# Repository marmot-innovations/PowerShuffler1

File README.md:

# PowerShuffler1
Summary: PowerShuffler1 is a HV isolated DC-DC charger PCBA for balancing weak cells within a large battery stack of Li-Ion cells.

Theory of operation: In a battery stack with 99 lithium-ion cells in series, there might be 1 or 2 weak cells that limit the usability of the entire battery pack. Let's assume the 99 li-ion cells are arranged in groups of 9 and there are certain groups that contain cells which are stronger than others. PowerShuffler1 is a PCBA that will piggy-back on top of the existing BMS that comes with the battery pack and draw power from the stronger group in order to charge up the 1 weak cell wherever it sits in the series of 99 cells. PowerShuffler1 has built-in intelligence not to over-discharge the stronger group by measuring the voltage of the 1 weak cell as it rises, and compares it to 1/9th of the stronger group's total voltage as it falls to within a certain threshold. Pre-programmed hysteresis prevents excessive start-stop charging as the cells are put through normal usage during the time when the existing BMS kicks in. Although intrusive, PowerShuffler1 is meant to be a diagnostics tool to verify and characterize weak cells within a battery stack on top of a pre-existing BMS. It does not replace the need for servicing the battery pack or using a better BMS down the road. PowerShuffler1 has no wired or wireless communication, which is not accessible anyway if piggy-backed within a battery pack enclosure.

Included in this project are:
1. Firmware for master MCU
2. Firmware for client MCU
3. PCB design for PCBA

Read the individual README for further details. Pictures will be added later to provide instructions for programming and installation, as well as board modifications where needed. Test data will be provided eventually.

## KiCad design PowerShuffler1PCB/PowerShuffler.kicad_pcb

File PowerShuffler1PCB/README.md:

## PowerShuffler 1.0 PCB design schematic, layout, Gerbers, and BOM  
KiCAD 5.0.0 for PCB design  
Microsoft Excel web for BOM  
No 3D model  
No XY pick and place Centroid  
No ODB++  
No footprint library  
No schematic library

Design bugs and comments:  
1. S2 pins 3 and 4 are swapped. Use wire wrap to un-swap them.
2. F2 will drop about 0.1V under full 500mA load when charging. No way to measure OCV in this version. Manually take measurements and compensate by adjusting master MCU.
3. R12 cannot be switched off to stop charging. Everytime the client MCU is turned on to take a measurement it will move energy.
4. To program master MCU, remove R6 and C7 first, then replace them once programming is completed. These components will put too much load on ISP TPI programmer.
5. To program client MCU, remove C24 and (optionally) R22 first, then replace them once completed. These components will put too much load on ISP TPI programmer.
6. J2 and J4 do not need soldered headers for programming. Just shove a 5-pin 0.1" straight strip header into it to establish electrical contact. Look up "sneaky footprints PCB" on the web.
7. Mounting holes are for 4-40 screws and stand-offs.
8. Peak 75% efficiency during max charge rate as measured.
9. Less than 0.5mA current draw from input when idle, not charging.

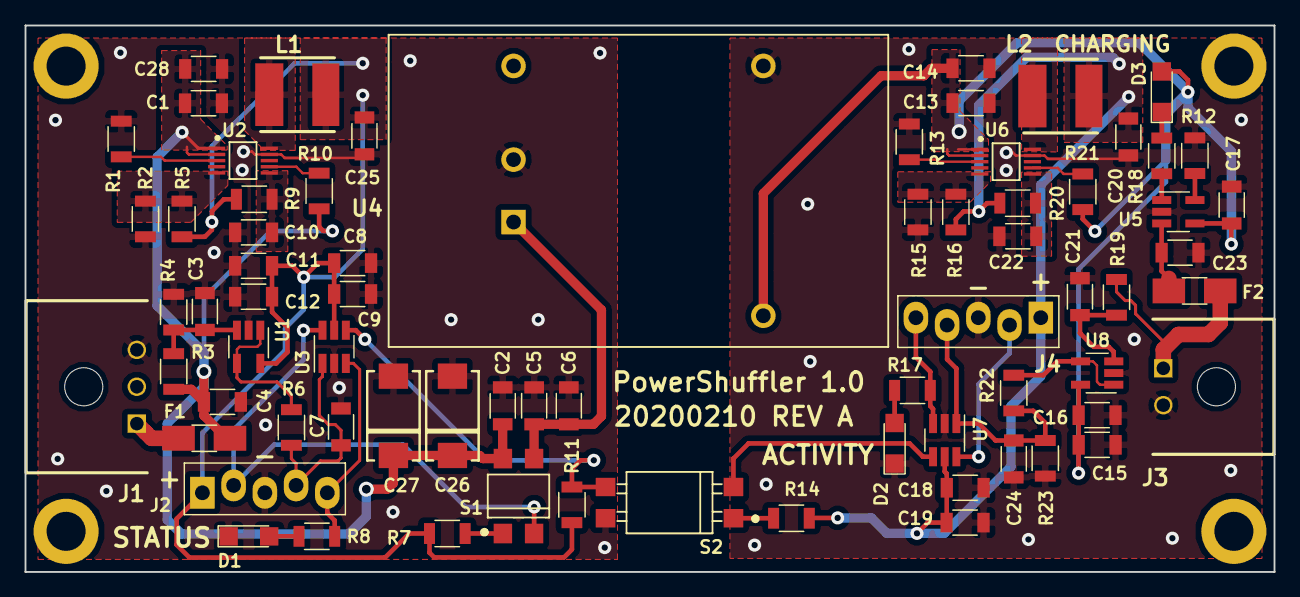
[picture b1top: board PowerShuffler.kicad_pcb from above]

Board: 4 copper layers, 101.6 x 44.5 mm, 76 parts (0 on the bottom side), 39 nets.

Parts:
C1, C3, C5, C7, C8, C11, C13, C15, C18, C21, C24: 1u; C_1206
C2, C6, C9, C12, C14, C16, C19, C28: 0.1u; C_1206
C4, C20, C25: 10u; C_1206
C10, C22: 0.22u; C_1206
C17, C23: 4.7u; C_1206
C26, C27: 15u; 2917
D1, D2, D3: LED; LED_1206
F1, F2: Fuse; Fuse_SMD1206_HandSoldering
J1: Conn_01x03; Molex_Microfit3_Header_3pin_Angled_43650
J2, J4: Conn_01x05; Staggered_ICSP_5x2.54mm_Straight
J3: Conn_01x02; Molex_Microfit3_Header_2pin_Angled_43650
L1, L2: 680u; SMD_Inductor_Shielded_6x6mm
MNT1, MNT2, MNT3, MNT4: MountingHole; 3mm_hole
R1, R10, R13, R21: 191k; R_1206
R2, R15: 49.9k; R_1206
R3: 150k; R_1206
R4, R22: 18.7k; R_1206
R5, R16: 158k; R_1206
R6, R7, R8, R14, R17, R19: 390; R_1206
R9, R20: 22.1; R_1206
R11, R12: 2k; R_1206
R18: 470; R_1206
R23: 56.2k; R_1206
S1: SSR4; SMD4_SSR_CPC1002N
S2: OPTOSOLO; SMD4_TL241AF-SSR_0.1_12x5mm
U1, U8: MCP6401; SOT-23-5_HandSoldering
U2, U6: SWITCHDCDCLOPOW; 10-μMAX_3x3mm
U3, U7: ATTINY; SOT-23-6_Handsoldering
U4: ISOLATEDDCDC; NSD05-S_6-DIP_1x1.6inch
U5: MCP73831; SOT-23-5_HandSoldering

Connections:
+3.3VA: C18.1, C19.1, C20.1, J4.1, L2.2, R14.1, R16.1, R20.1, U7.5
+3V3: C8.1, C9.1, C11.1, C12.1, C25.1, J2.1, L1.2, R5.1, R7.2, R9.1, R11.1, U1.5, U3.5
+5VA: C13.1, C14.1, C15.1, C16.1, C17.1, D3.2, R21.2, U4.3, U5.4, U6.1, U6.2, U8.5
+36V: C1.1, C2.1, C4.1, C26.1, C27.1, C28.1, F1.1, R3.1, R10.2, S1.4, U2.1, U2.2
/36VSWITCH: C5.1, C6.1, S1.3, U4.1
/PB0_1: C7.1, J2.4, R6.1, U3.1
/PB0_2: C24.1, J4.4, R22.2, R23.1, U7.1
/PB1_1: J2.5, R8.1, U3.3
/PB1_2: J4.5, R17.1, U7.3
/PB2_1: R11.2, S2.3, U3.4
/PB2_2: S2.2, U7.4
/PB3_1: J2.2, S1.2, U3.6
/PB3_2: J4.2, U7.6
/VBATT: F2.1, J3.1, R19.2
/VBATTFUSE: C23.1, F2.2, U5.3
/VSUBSHEET: C3.1, R3.2, R4.1, U1.3
GND: C1.2, C2.2, C3.2, C4.2, C5.2, C6.2, C7.2, C8.2, C9.2, C10.2, C11.2, C12.2, C25.2, C26.2, C27.2, C28.2, D1.1, J1.3, J2.3, R1.2, R2.1, R4.2, S2.4, U1.2, U2.9, U3.2, U4.2
GNDA: C13.2, C14.2, C15.2, C16.2, C17.2, C18.2, C19.2, C20.2, C21.2, C22.2, C23.2, C24.2, D2.1, J3.2, J4.3, R12.1, R13.2, R15.1, R23.2, U4.4, U5.2, U6.9, U7.2, U8.2
unnamed: C10.1, R9.2, U2.6
unnamed: C21.1, R19.1, U8.3
unnamed: C22.1, R20.2, U6.6
unnamed: D1.2, R8.2
unnamed: D2.2, R17.2
unnamed: D3.1, R18.2
unnamed: F1.2, J1.1
unnamed: L1.1, U2.10
unnamed: L2.1, U6.10
unnamed: R1.1, U2.3
unnamed: R2.2, R5.2, U2.5
unnamed: R6.2, U1.1, U1.4
unnamed: R7.1, S1.1
unnamed: R10.1, U2.7
unnamed: R12.2, U5.5
unnamed: R13.1, U6.3
unnamed: R14.2, S2.1
unnamed: R15.2, R16.2, U6.5
unnamed: R18.1, U5.1
unnamed: R21.1, U6.7
unnamed: R22.1, U8.1, U8.4

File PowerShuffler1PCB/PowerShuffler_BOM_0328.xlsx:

ref | QTY | value5 | footprint | Manuf P/N | Digikey P/N | description
U2, U6 | 2 | SWITCHDCDCLOPOW | BMB:10-μMAX_3x3mm | MAX17550AUB+ | MAX17550AUB+-ND | IC REG BUCK ADJ 25MA 10UMAX
C26, C27 | 2 | 15u | BMB:2917 | TR3E156M050C0300‎ | 718-1785-1-ND‎ | CAP TANT 15UF 20% 50V 2917
J3 | 1 | Conn_01x02 | BMB:Molex_Microfit3_Header_2pin_Angled_43650 | 0436500200‎ | WM1860-ND | CONN HEADER R/A 2POS 3MM
J1 | 1 | Conn_01x03 | BMB:Molex_Microfit3_Header_3pin_Angled_43650 | 0436500301‎ | ‎WM1866-ND‎ | CONN HEADER R/A 3POS 3MM
U4 | 1 | ISOLATEDDCDC | BMB:NSD05-S_6-DIP_1x1.6inch | NSD05-48S5‎ | 1866-3621-ND‎ | DC DC CONVERTER 5V 5W isolated
L1, L2 | 2 | 680u | BMB:SMD_Inductor_Shielded_6x6mm | VLS6045EX-681M | ‎445-180928-1-ND | FIX IND 680UH 320MA 2.95OHM SMD
S1 | 1 | SSR4 | BMB:SMD4_SSR_CPC1002N | CPC1002NTR‎ | CLA230CT-ND | SSR RELAY SPST-NO 700MA 0-60V
S2 | 1 | OPTOSOLO | BMB:SMD4_TL241AF-SSR_0.1_12x5mm | ‎LTV-816S | ‎160-1361-5-ND | OPTOISOLATR 5KV TRANSISTOR 4-SMD
J2 | 1 | Conn_01x05 | BMB:Staggered_ICSP_5x2.54mm_Straight |  |  | DO NOT POPULATE
J4 | 1 | Conn_01x05 | BMB:Staggered_ICSP_5x2.54mm_Straight |  |  | DO NOT POPULATE
C12, C14, C16, C19, C2, C28, C6, C9 | 8 | 0.1u | Capacitors_SMD:C_1206 | CL31B104KCFNNNE‎ | 1276-1151-1-ND | CAP CER 0.1UF 100V X7R 1206
C10, C22 | 2 | 0.22u | Capacitors_SMD:C_1206 | CL31B224KBFNNNE‎ | 1276-1106-1-ND
C20, C25, C4 | 3 | 10u | Capacitors_SMD:C_1206 | CL31B106KBHNNNE‎ | 1276-6767-1-ND | CAP CER 10UF 50V X7R 1206
C1, C11, C13, C15, C18, C21, C24, C3, C5, C7, C8 | 11 | 1u | Capacitors_SMD:C_1206 | CL31B105KBHNNNE‎ | ‎1276-1068-1-ND‎ | CAP CER 1UF 50V X7R 1206
C17, C23 | 2 | 4.7u | Capacitors_SMD:C_1206 | CL31B475KAHNNWE‎ | ‎1276-3178-1-ND
F1 | 1 | Fuse | Fuse_Holders_and_Fuses:Fuse_SMD1206_HandSoldering | C1F 3 | 507-1883-1-ND | FUSE 3.0A 125VAC FAST 1206
F2 | 1 | Fuse | Fuse_Holders_and_Fuses:Fuse_SMD1206_HandSoldering | C1F 1.5 | 507-1880-1-ND | FUSE 1.5A 125VAC FAST 1206
D1 | 1 | LED | LEDs:LED_1206 | 150120GS75000‎ | ‎732-4990-1-ND‎ | LED GREEN CLEAR 1206 SMD
D2, D3 | 2 | LED | LEDs:LED_1206 | 150120RS75000‎ | ‎732-4991-1-ND | LED RED CLEAR 1206 SMD
R20, R9 | 2 | 22.1 | Resistors_SMD:R_1206 | RMCF1206FT22R1‎ | ‎RMCF1206FT22R1CT-ND‎
R14, R17, R19, R6, R7, R8 | 6 | 390 | Resistors_SMD:R_1206 | RMCF1206JT390R‎ | ‎RMCF1206JT390RCT-ND‎
R18 | 1 | 470 | Resistors_SMD:R_1206 | RMCF1206JT470R‎ | ‎RMCF1206JT470RCT-ND‎
R3 | 1 | 210k | Resistors_SMD:R_1206 | ERA-8AEB2103V | P210KBCCT-ND | RES SMD 210K OHM 0.1% 1/4W 1206
R16, R5 | 2 | 158k | Resistors_SMD:R_1206 | RMCF1206FT158K‎ | ‎RMCF1206FT158KCT-ND‎ | RES 158K OHM 1% 1/4W 1206
R22 | 1 | 18.7k | Resistors_SMD:R_1206 | ‎ERA-8AEB1872V‎ | ‎P18.7KBCCT-ND‎ | RES SMD 18.7K OHM 0.1% 1/4W 1206
R4 | 1 | 19.1k | Resistors_SMD:R_1206 | ‎RT1206BRD0719K1L | YAG2018CT-ND‎ | RES SMD 19.1K OHM 0.1% 1/4W 1206
R1, R10, R13, R21 | 4 | 191k | Resistors_SMD:R_1206 | MCR18ERTF1913‎ | ‎RHM191KCJCT-ND‎ | RES SMD 191K OHM 1% 1/4W 1206
R11, R12, R18 | 3 | 2k | Resistors_SMD:R_1206 | RMCF1206FG2K00‎ | ‎RMCF1206FG2K00CT-ND‎ | RES 2K OHM 1% 1/4W 1206
R15, R2 | 2 | 49.9k | Resistors_SMD:R_1206 | RMCF1206FT49K9‎ | ‎RMCF1206FT49K9CT-ND‎ | RES 49.9K OHM 1% 1/4W 1206
R23 | 1 | 56.2k | Resistors_SMD:R_1206 | RT1206BRD0756K2L‎ | YAG2060CT-ND | RES SMD 56.2K OHM 0.1% 1/4W 1206
U1, U8 | 2 | MCP6401 | TO_SOT_Packages_SMD:SOT-23-5_HandSoldering | ‎MCP6401T-H/OT‎ | MCP6401T-H/OTCT-ND‎ | IC OPAMP GP 1 CIRCUIT SOT23-5 hi temp
U5 | 1 | MCP73831 | TO_SOT_Packages_SMD:SOT-23-5_HandSoldering | ‎MCP73831T-2DCI/OT‎ | ‎MCP73831T-2DCI/OTCT-ND‎ | IC CONTROLLR LI-ION 4.2V SOT23-5
U3, U7 | 2 | ATTINY | TO_SOT_Packages_SMD:SOT-23-6_Handsoldering | ‎ATTINY10-TSHR‎ | ‎ATTINY10-TSHRCT-ND‎ | IC MCU 8BIT 1KB FLASH SOT23

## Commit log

2020-05-03 Update README for high level project
2020-05-03 Create README for PowerShuffler1 PCB
2020-05-03 Add PCB design files, KiCAD and BOM
2020-05-03 Create README for gerbers
2020-05-03 Add PCB design files, gerbers
2020-05-03 Create README for master MCU fw
2020-05-03 Add AtmelStudio project files, master MCU fw
2020-05-03 Add AtmelStudio source files, master MCU fw
2020-05-03 Update README with mcu details
2020-05-03 Create README for client MCU fw
2020-05-03 Add AtmelStudio project files, client MCU fw
2020-05-03 Add AtmelStudio source files, client MCU fw
2020-05-03 was used to create folder. file not needed.
2020-05-03 Update formatting
2020-05-03 Update formatting, bold headline
2020-05-04 Add PCB design drawings and schematic PDF
